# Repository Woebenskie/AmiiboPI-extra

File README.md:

# AmiiboPI-extra
Fusion360 and Eagle files for the AmiiboPI project

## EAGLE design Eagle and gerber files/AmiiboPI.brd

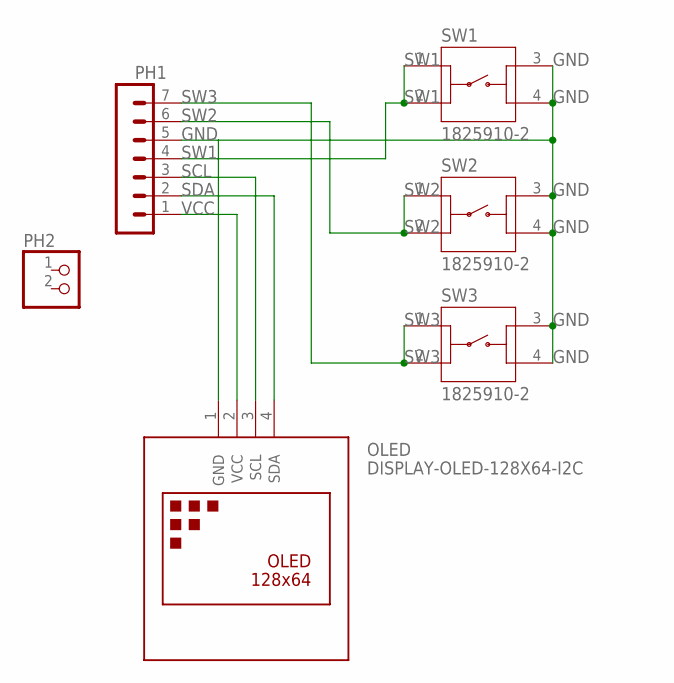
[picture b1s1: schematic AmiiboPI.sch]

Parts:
OLED: DISPLAY-OLED-128X64-I2C
PH1: MA07-1
PH2: PINHD-1X2; 1X02
SW1, SW2, SW3: 1825910-2; TE_1825910-2

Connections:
GND: OLED.1 (GND), PH1.5, SW1.3, SW1.4, SW2.3, SW2.4, SW3.3, SW3.4
SCL: OLED.3 (SCL), PH1.3
SDA: OLED.4 (SDA), PH1.2
SW1: PH1.4, SW1.1, SW1.2
SW2: PH1.6, SW2.1, SW2.2
SW3: PH1.7, SW3.1, SW3.2
VCC: OLED.2 (VCC), PH1.1

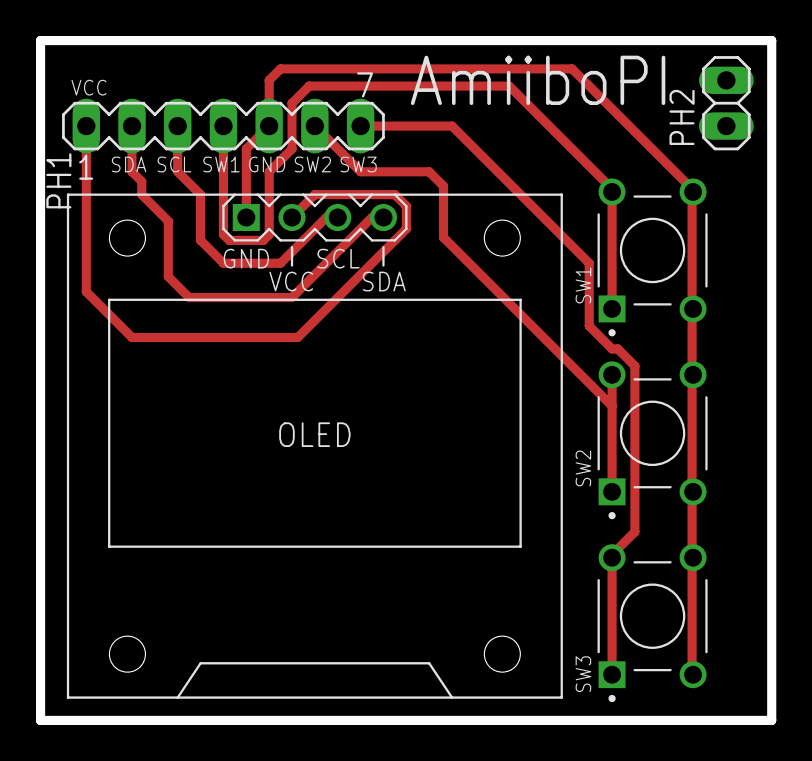
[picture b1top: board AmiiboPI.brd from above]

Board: 2 copper layers, 40.6 x 37.8 mm, 6 parts (0 on the bottom side), 7 nets.

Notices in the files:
parts and their libraries:
diy-modules: Released under the Creative Commons Attribution 4.0 International License: http://creativecommons.org/licenses/by/4.0
